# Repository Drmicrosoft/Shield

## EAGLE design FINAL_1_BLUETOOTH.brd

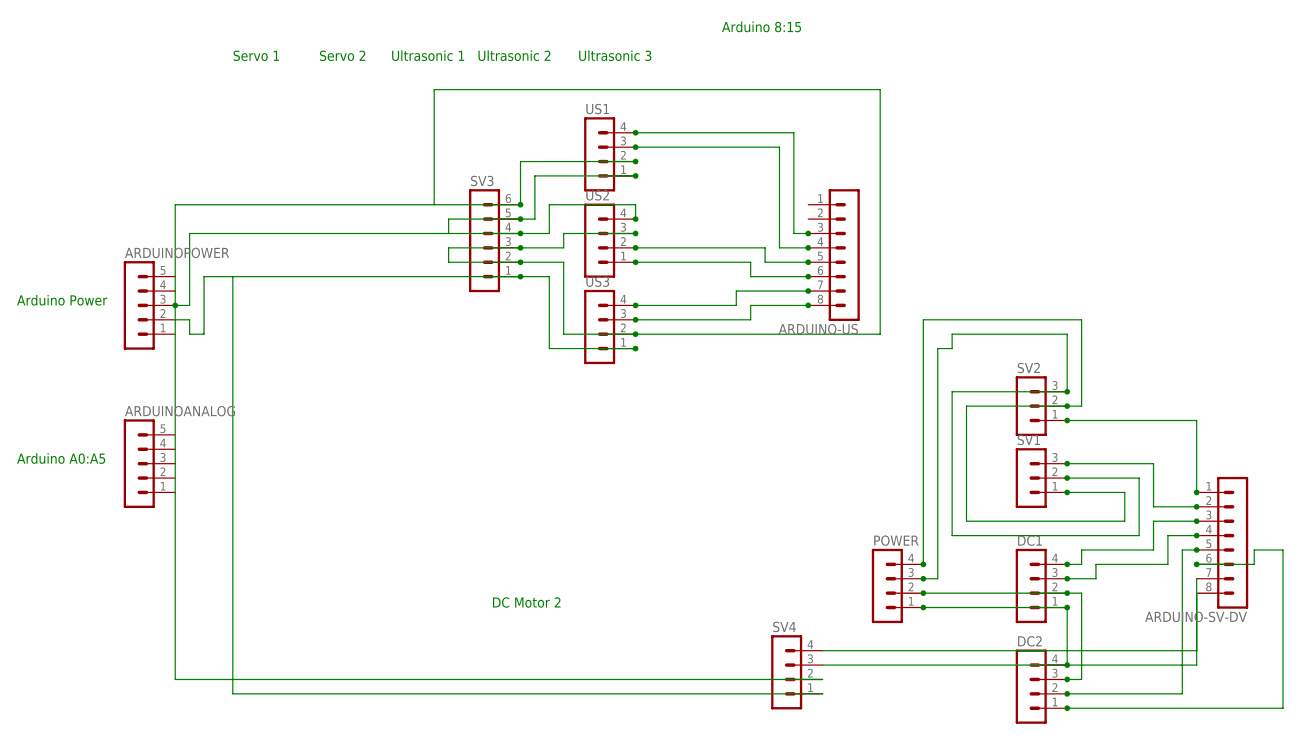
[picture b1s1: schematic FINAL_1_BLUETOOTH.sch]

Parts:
ARDUINO-SV-DV: MA08-1W
ARDUINO-US: MA08-1W
ARDUINOANALOG: MA05-1
ARDUINOPOWER: MA05-1
DC1, DC2: MA04-1
POWER: MA04-1
SV1, SV2: MA03-1
SV3: MA06-1
SV4: MA04-1
US1, US2, US3: MA04-1

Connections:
5V2: POWER.3, SV1.2, SV2.3
5V3: DC1.1, DC2.4, POWER.1
5VSS: ARDUINOPOWER.4, SV3.2, SV3.3, SV3.6, SV4.2, US1.2, US2.3, US3.2
GND2: POWER.4, SV1.1, SV2.2
GND3: DC1.2, DC2.3, POWER.2
GNDSS: ARDUINOPOWER.2, SV3.1, SV4.1, US3.1
unnamed: ARDUINO-SV-DV.8, SV4.4
unnamed: ARDUINO-SV-DV.7, SV4.3
SGN3: ARDUINO-SV-DV.3, DC1.4
SGN4: ARDUINO-SV-DV.4, DC1.3
SGN5: ARDUINO-SV-DV.5, DC2.2
SGN6: ARDUINO-SV-DV.6, DC2.1
SGNN2: ARDUINO-SV-DV.2, SV1.3
SIG1: ARDUINO-SV-DV.1, SV2.1
US1: ARDUINO-US.3, US1.4
US2: ARDUINO-US.4, US1.3
US3: ARDUINO-US.5, US2.2
US4: ARDUINO-US.6, US2.1
US5: ARDUINO-US.7, US3.4
US6: ARDUINO-US.8, US3.3
USGND: ARDUINOPOWER.3, SV3.4, SV3.5, US1.1, US2.4

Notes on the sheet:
Servo 1
Servo 2
Ultrasonic 1
Ultrasonic 2
Ultrasonic 3
DC Motor 2
Arduino 8:15
Arduino A0:A5
Arduino Power

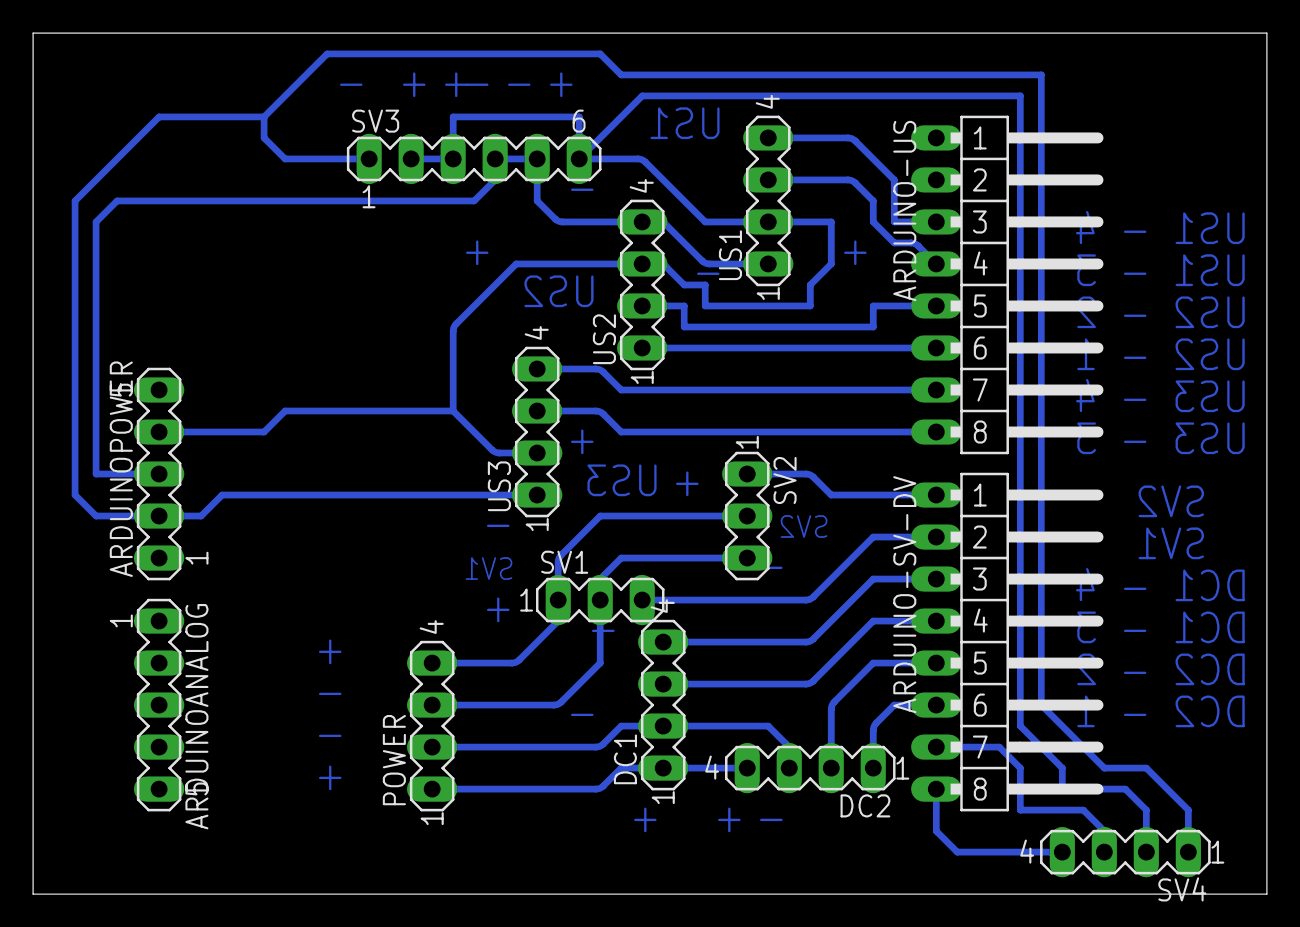
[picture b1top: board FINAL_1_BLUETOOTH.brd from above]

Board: 2 copper layers, 74.6 x 52.1 mm, 14 parts (0 on the bottom side), 21 nets.

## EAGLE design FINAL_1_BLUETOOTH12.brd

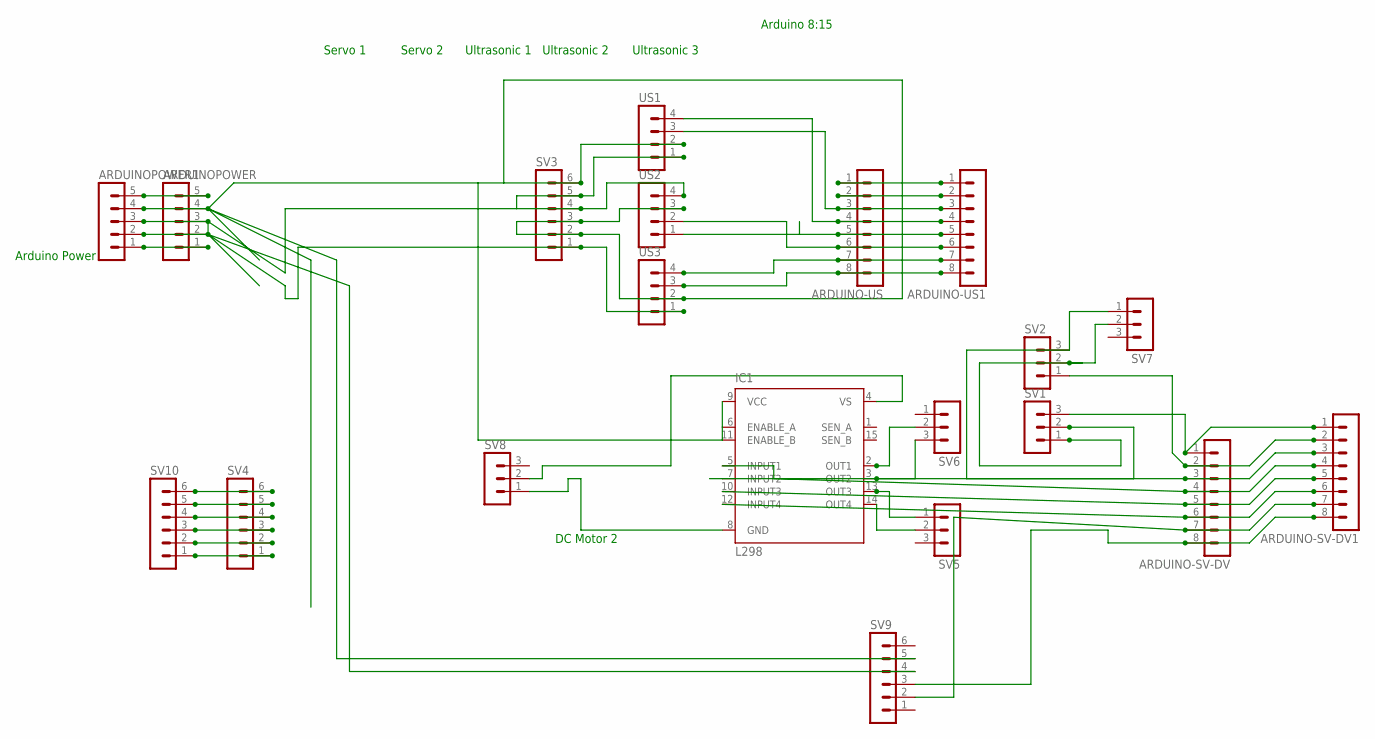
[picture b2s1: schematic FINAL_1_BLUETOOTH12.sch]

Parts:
ARDUINO-SV-DV, ARDUINO-SV-DV1: MA08-1W
ARDUINO-US, ARDUINO-US1: MA08-1W
ARDUINOPOWER, ARDUINOPOWER1: MA05-1
IC1: L298; MULTIWATT-15
SV1, SV2, SV5, SV6, SV7, SV8: MA03-1
SV3, SV4, SV9, SV10: MA06-1
US1, US2, US3: MA04-1

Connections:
5V2: SV1.2, SV2.3, SV7.1
5VSS: ARDUINOPOWER.4, ARDUINOPOWER1.4, IC1.6 (ENABLE_A), IC1.9 (VCC), IC1.11 (ENABLE_B), SV3.2, SV3.3, SV3.6, SV9.5, US1.2, US2.3, US3.2
GND2: ARDUINOPOWER.2, ARDUINOPOWER.3, ARDUINOPOWER1.2, ARDUINOPOWER1.3, SV3.1, SV3.4, SV3.5, SV9.4, US1.1, US2.4, US3.1
unnamed: ARDUINO-SV-DV.8, ARDUINO-SV-DV1.8, SV9.3
unnamed: ARDUINO-SV-DV.7, ARDUINO-SV-DV1.7, SV9.2
unnamed: IC1.2 (OUT1), SV6.2
unnamed: IC1.8 (GND), SV8.1
unnamed: IC1.4 (VS), SV8.2
unnamed: IC1.3 (OUT2), SV6.3
unnamed: IC1.13 (OUT3), SV5.1
unnamed: IC1.14 (OUT4), SV5.2
unnamed: ARDUINO-US.2, ARDUINO-US1.2
unnamed: ARDUINO-SV-DV.4, ARDUINO-SV-DV1.4, IC1.5 (INPUT1)
unnamed: ARDUINO-SV-DV.3, ARDUINO-SV-DV1.3, IC1.7 (INPUT2)
unnamed: ARDUINO-SV-DV.5, ARDUINO-SV-DV1.5, IC1.10 (INPUT3)
unnamed: ARDUINO-SV-DV.2, ARDUINO-SV-DV1.2, SV2.1
unnamed: SV1.1, SV2.2, SV7.2
unnamed: ARDUINO-US.1, ARDUINO-US1.1
unnamed: ARDUINOPOWER.5, ARDUINOPOWER1.5
unnamed: SV4.6, SV10.6
unnamed: SV4.4, SV10.4
unnamed: SV4.5, SV10.5
unnamed: SV4.3, SV10.3
unnamed: SV4.2, SV10.2
unnamed: SV4.1, SV10.1
unnamed: ARDUINO-SV-DV.1, ARDUINO-SV-DV1.1, SV1.3
unnamed: ARDUINOPOWER.1, ARDUINOPOWER1.1
SGN6: ARDUINO-SV-DV.6, ARDUINO-SV-DV1.6, IC1.12 (INPUT4)
US1: ARDUINO-US.3, ARDUINO-US1.3, US1.3
US2: ARDUINO-US.4, ARDUINO-US1.4, US1.4
US3: ARDUINO-US.5, ARDUINO-US1.5, US2.1
US4: ARDUINO-US.6, ARDUINO-US1.6, US2.2
US5: ARDUINO-US.7, ARDUINO-US1.7, US3.4
US6: ARDUINO-US.8, ARDUINO-US1.8, US3.3

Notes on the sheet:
Servo 1
Servo 2
Ultrasonic 1
Ultrasonic 2
Ultrasonic 3
DC Motor 2
Arduino 8:15
Arduino Power

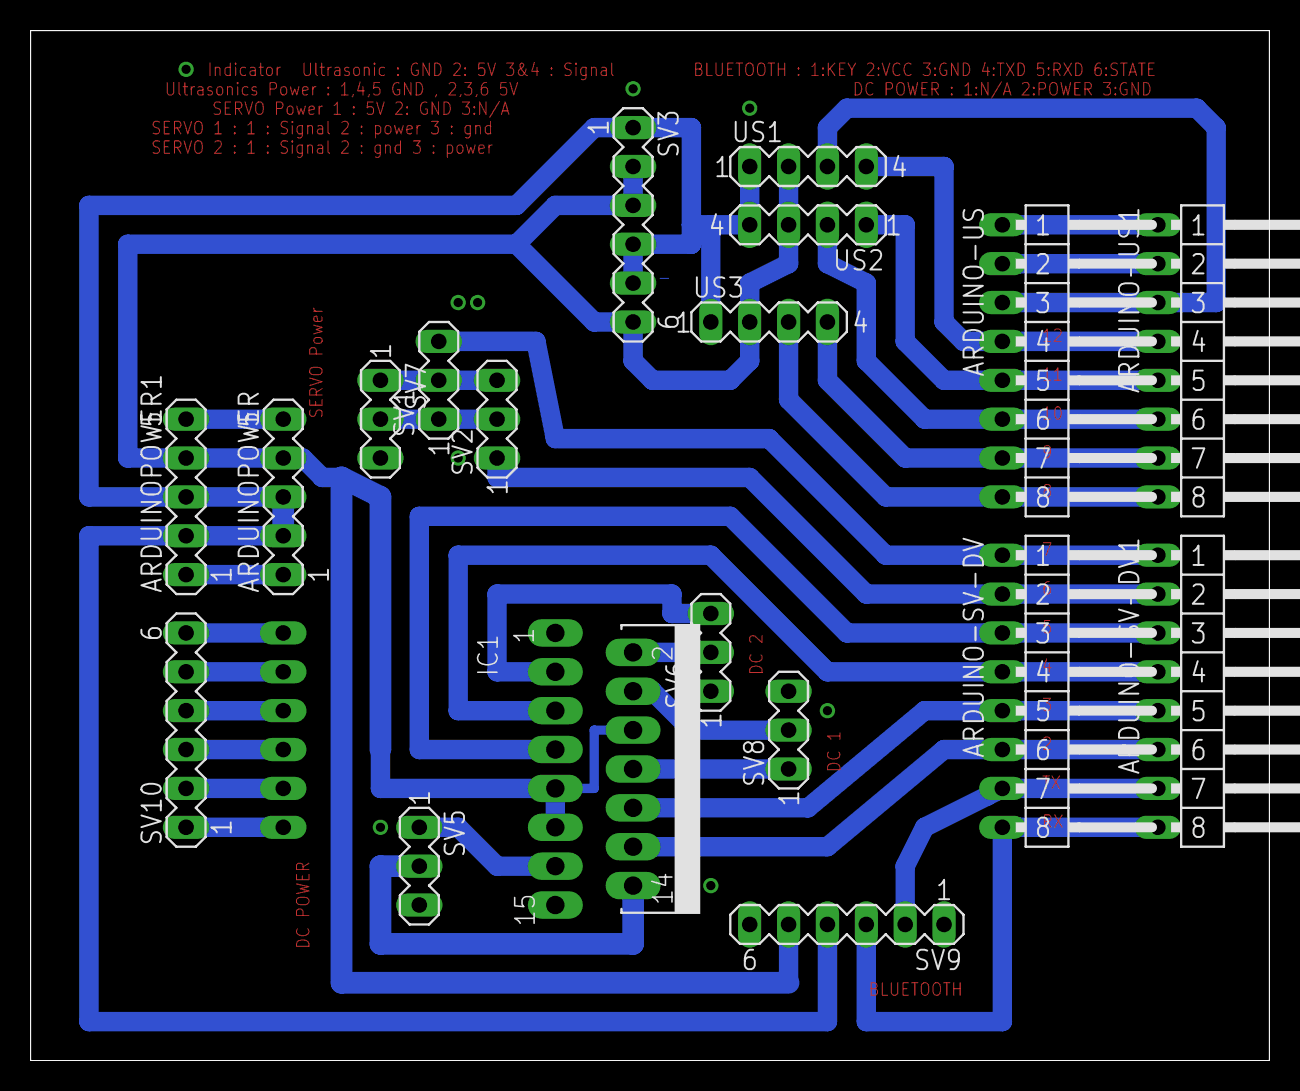
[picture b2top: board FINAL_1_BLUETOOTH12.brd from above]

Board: 2 copper layers, 81.0 x 67.3 mm, 20 parts (1 on the bottom side), 34 nets.
